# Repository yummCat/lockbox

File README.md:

# lockbox

The latest brilliant innovation we were able to come up with, was a box, that locks! 🤯

This device was meant to be small and cute, and importantly baby friendly. Designed for baby professionals, colloquially known as "Boss Babies" this device is meant to be carried around in a briefcase, unlocked with an RFID badge and four digit pin. In the process we learned a lot about RFID and how encryption worked(when we got sidetracked).

This project started with a schematic:

Next we made the pcb design:

Next we made the 3d model:

Lastly the BOM:

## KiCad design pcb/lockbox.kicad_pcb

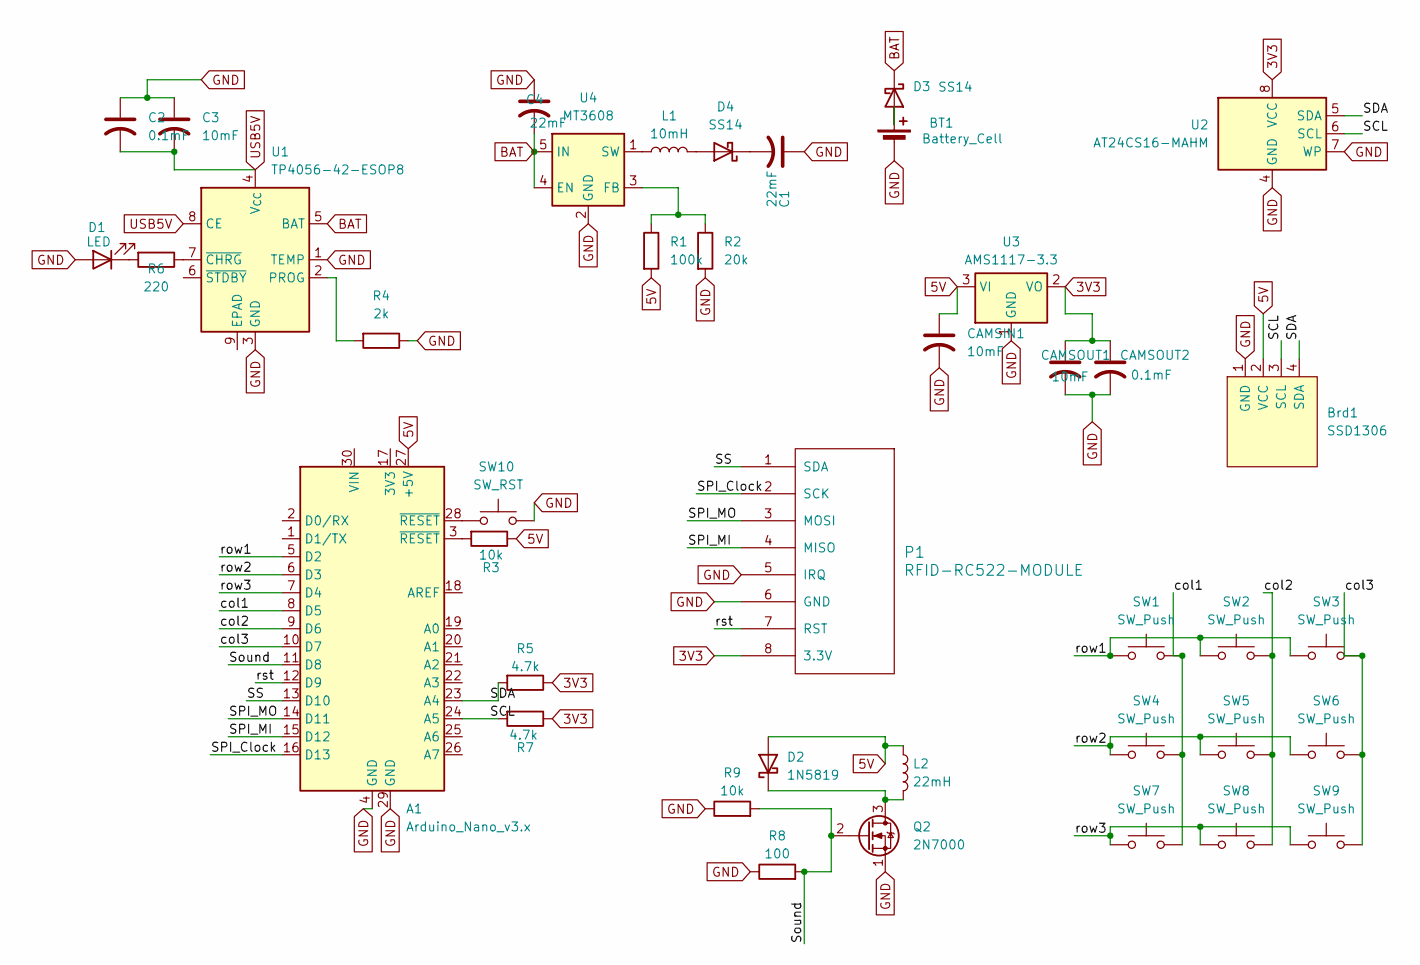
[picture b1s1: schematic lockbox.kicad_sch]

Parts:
A1: Arduino_Nano_v3.x; Arduino_Nano
BT1: Battery_Cell; JST_PH_S2B-PH-K_1x02_P2.00mm_Horizontal
Brd1: SSD1306; Adafruit_SSD1306
C1, C4: 22mF; CP_Radial_D5.0mm_P2.00mm
C2: 0.1mF; CP_Radial_D5.0mm_P2.50mm
C3: 10mF; CP_Radial_D5.0mm_P2.00mm
CAMSIN1: 10mF; CP_Radial_D5.0mm_P2.00mm
CAMSOUT1: 10mF; CP_Radial_D5.0mm_P2.00mm
CAMSOUT2: 0.1mF; CP_Radial_D5.0mm_P2.50mm
D1: LED; LED_D5.0mm
D2: 1N5819; D_DO-41_SOD81_P10.16mm_Horizontal
D3, D4: SS14; D_SMA
L1: 10mH; L_Axial_L26.0mm_D9.0mm_P5.08mm_Vertical_Fastron_77A
L2: 22mH; L_Axial_L26.0mm_D9.0mm_P5.08mm_Vertical_Fastron_77A
P1: RFID-RC522-MODULE; RC522_I2C_B30x20mm
Q2: 2N7000; TO-92L_Inline_Wide
R1: 100k; R_Axial_DIN0207_L6.3mm_D2.5mm_P7.62mm_Horizontal
R2: 20k; R_Axial_DIN0207_L6.3mm_D2.5mm_P7.62mm_Horizontal
R3, R9: 10k; R_Axial_DIN0207_L6.3mm_D2.5mm_P7.62mm_Horizontal
R4: 2k; R_Axial_DIN0207_L6.3mm_D2.5mm_P7.62mm_Horizontal
R5, R7: 4.7k; R_Axial_DIN0207_L6.3mm_D2.5mm_P7.62mm_Horizontal
R6: 220; R_Axial_DIN0207_L6.3mm_D2.5mm_P7.62mm_Horizontal
R8: 100; R_Axial_DIN0207_L6.3mm_D2.5mm_P7.62mm_Horizontal
SW1, SW2, SW3, SW4, SW5, SW6, SW7, SW8, SW9: SW_Push; SW_Cherry_MX_1.00u_PCB
SW10: SW_RST; SW_Cherry_MX_1.00u_PCB
U1: TP4056-42-ESOP8; SOIC-8-1EP_3.9x4.9mm_P1.27mm_EP2.41x3.3mm_ThermalVias
U2: AT24CS16-MAHM; DFN-8-1EP_3x2mm_P0.5mm_EP1.3x1.5mm
U3: AMS1117-3.3; SOT-223-3_TabPin2
U4: MT3608; SOT-23-6

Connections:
3V3: CAMSOUT1.1, CAMSOUT2.1, P1.8 (3.3V), R5.1, R7.1, U2.8 (VCC), U3.2 (VO)
5V: A1.27 (+5V), Brd1.2 (VCC), CAMSIN1.1, D2.2 (A), L2.1, R1.2, R3.1, U3.3 (VI)
/SCL: A1.24 (A5), Brd1.3 (SCL), R7.2, U2.6 (SCL)
/SDA: A1.23 (A4), Brd1.4 (SDA), R5.2, U2.5 (SDA)
/SPI_Clock: A1.16 (D13), P1.2 (SCK)
/SPI_MI: A1.15 (D12), P1.4 (MISO)
/SPI_MO: A1.14 (D11), P1.3 (MOSI)
/SS: A1.13 (D10), P1.1 (SDA)
/Sound: A1.11 (D8), Q2.2 (G), R8.2, R9.2
/col1: A1.8 (D5), SW1.2, SW4.2, SW7.2
/col2: A1.9 (D6), SW2.2, SW5.2, SW8.2
/col3: A1.10 (D7), SW3.2, SW6.2, SW9.2
/row1: A1.5 (D2), SW1.1, SW2.1, SW3.1
/row2: A1.6 (D3), SW4.1, SW5.1, SW6.1
/row3: A1.7 (D4), SW7.1, SW8.1, SW9.1
/rst: A1.12 (D9), P1.7 (RST)
BAT: C4.2, D3.1 (K), U1.5 (BAT), U4.4 (EN), U4.5 (IN)
GND: A1.4 (GND), A1.29 (GND), BT1.2 (-), Brd1.1 (GND), C1.1, C2.1, C3.1, C4.1, CAMSIN1.2, CAMSOUT1.2, CAMSOUT2.2, D1.2 (A), P1.5 (IRQ), P1.6 (GND), Q2.1 (S), R2.2, R4.1, R8.1, R9.1, SW10.2, U1.1 (TEMP), U1.3 (GND), U2.4 (GND), U2.7 (WP), U3.1 (GND), U4.2 (GND)
unnamed: A1.3 (~RESET), R3.2
unnamed: A1.28 (~RESET), SW10.1
unnamed: BT1.1 (+), D3.2 (A)
unnamed: D1.1 (K), R6.2
unnamed: D2.1 (K), L2.2, Q2.3 (D)
unnamed: D4.2 (A), L1.2
unnamed: C1.2, D4.1 (K)
unnamed: R4.2, U1.2 (PROG)
unnamed: R6.1, U1.7 (~CHRG)
unnamed: R1.1, R2.1, U4.3 (FB)
unnamed: L1.1, U4.1 (SW)
USB5V: C2.2, C3.2, U1.4 (V_{CC}), U1.8 (CE)

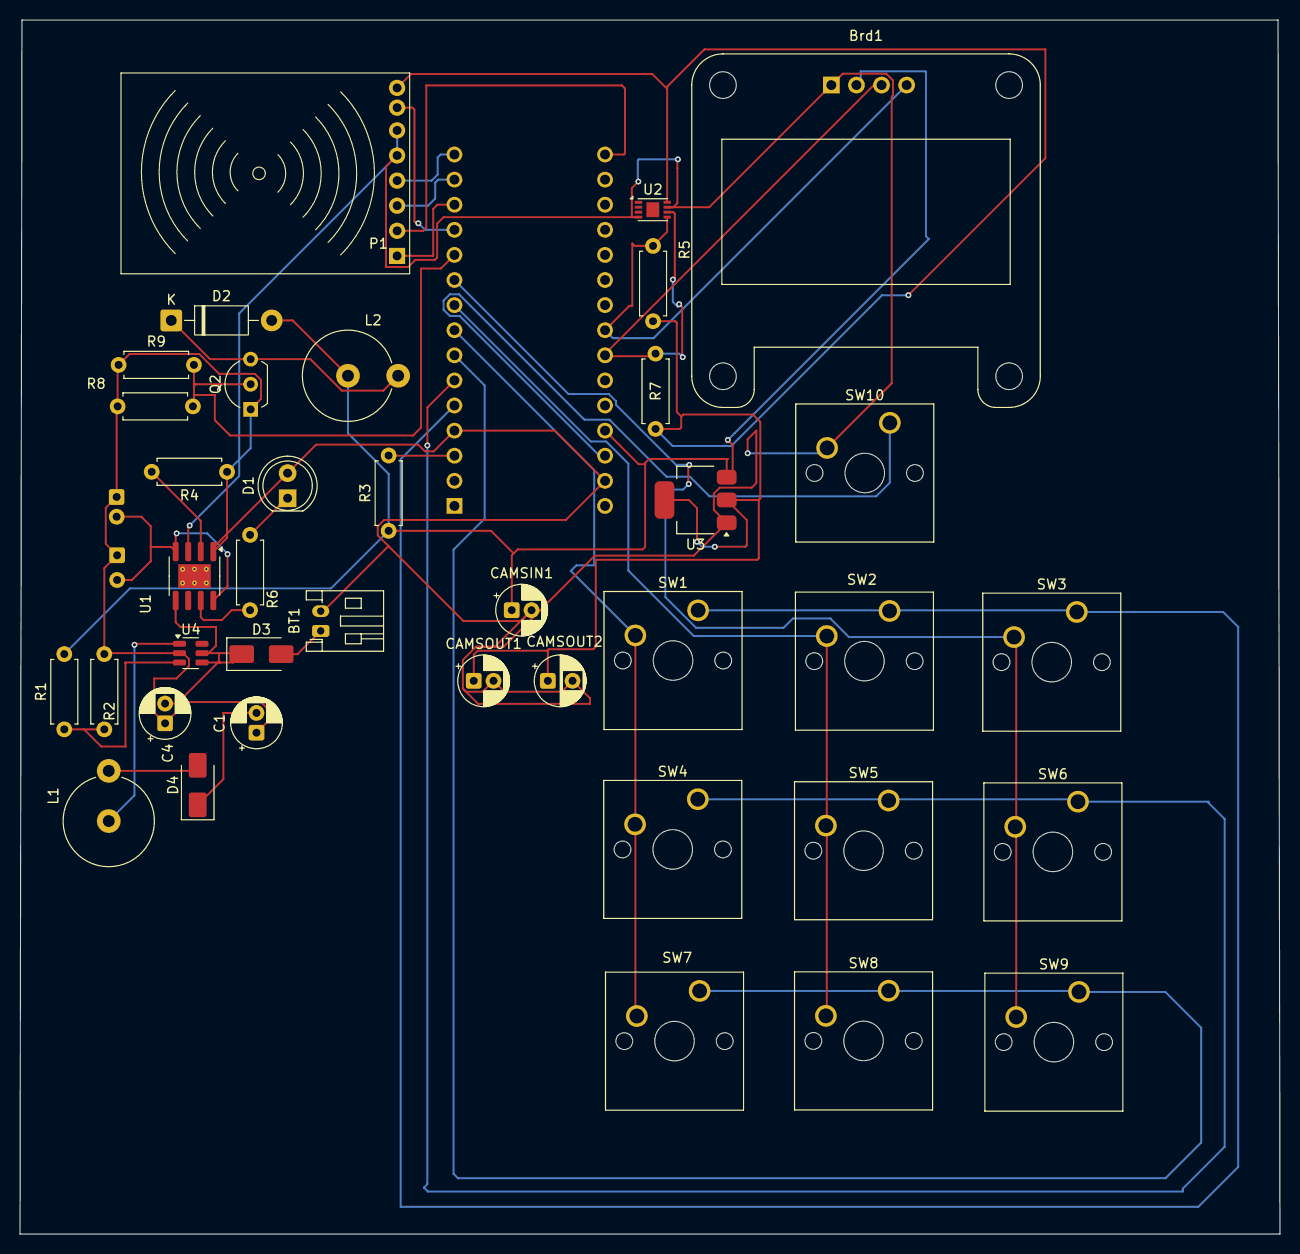
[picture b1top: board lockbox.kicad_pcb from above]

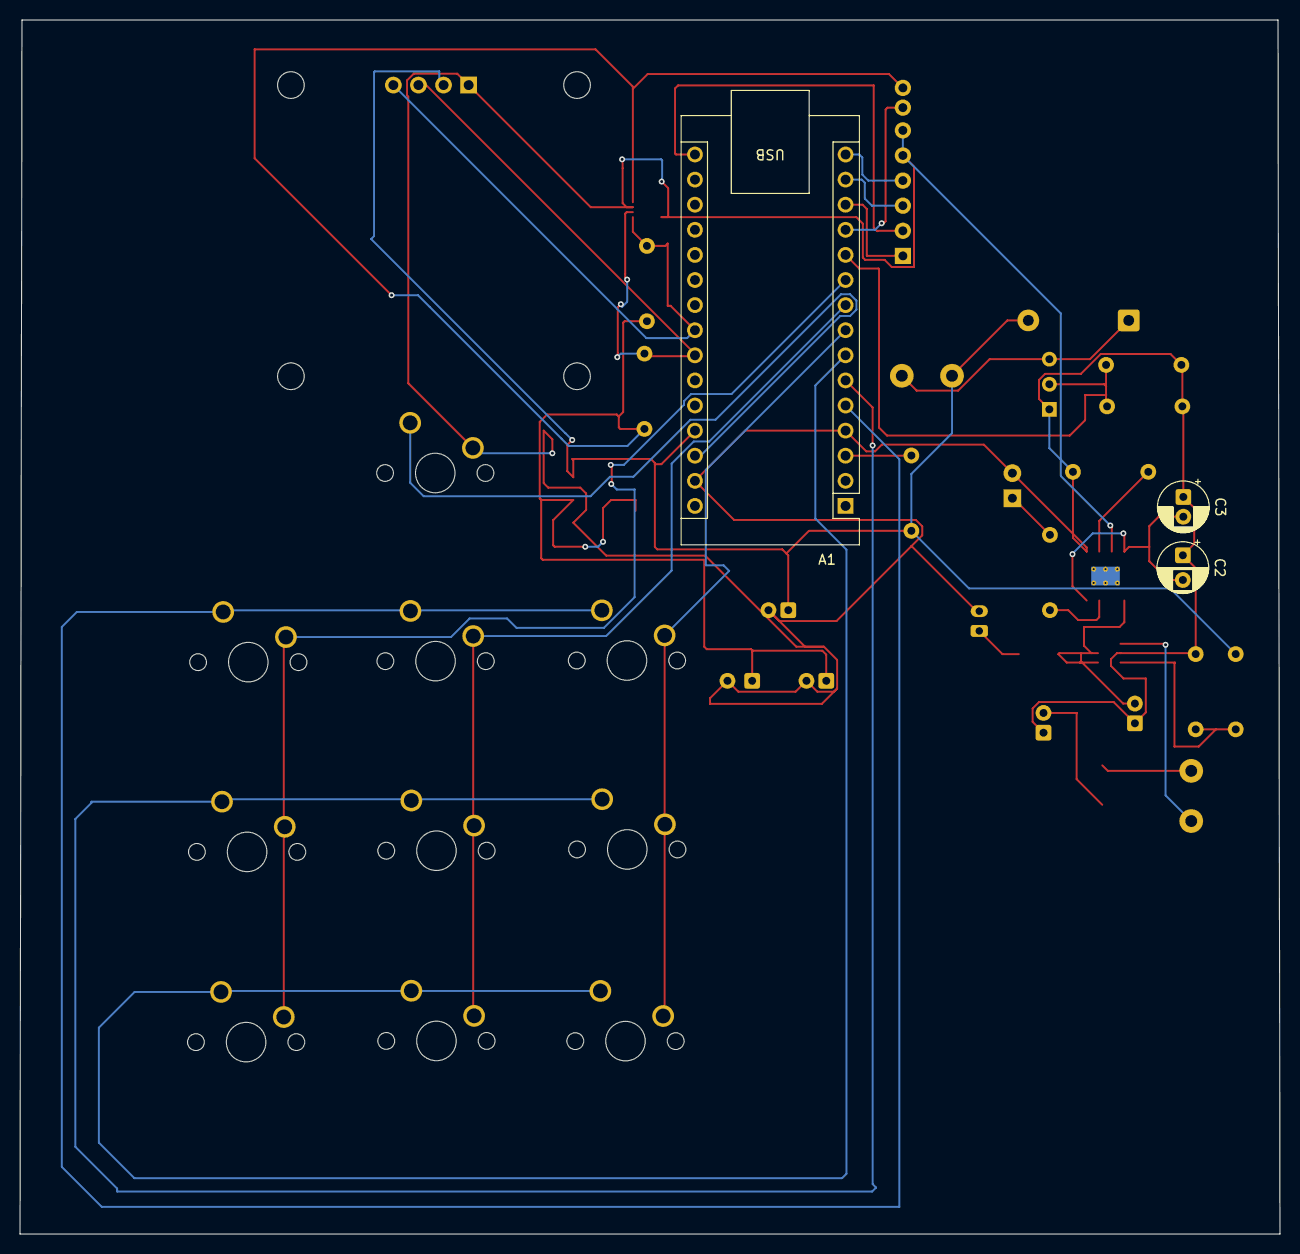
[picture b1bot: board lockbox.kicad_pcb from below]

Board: 2 copper layers, 127.5 x 122.8 mm, 41 parts (3 on the bottom side), 30 nets.

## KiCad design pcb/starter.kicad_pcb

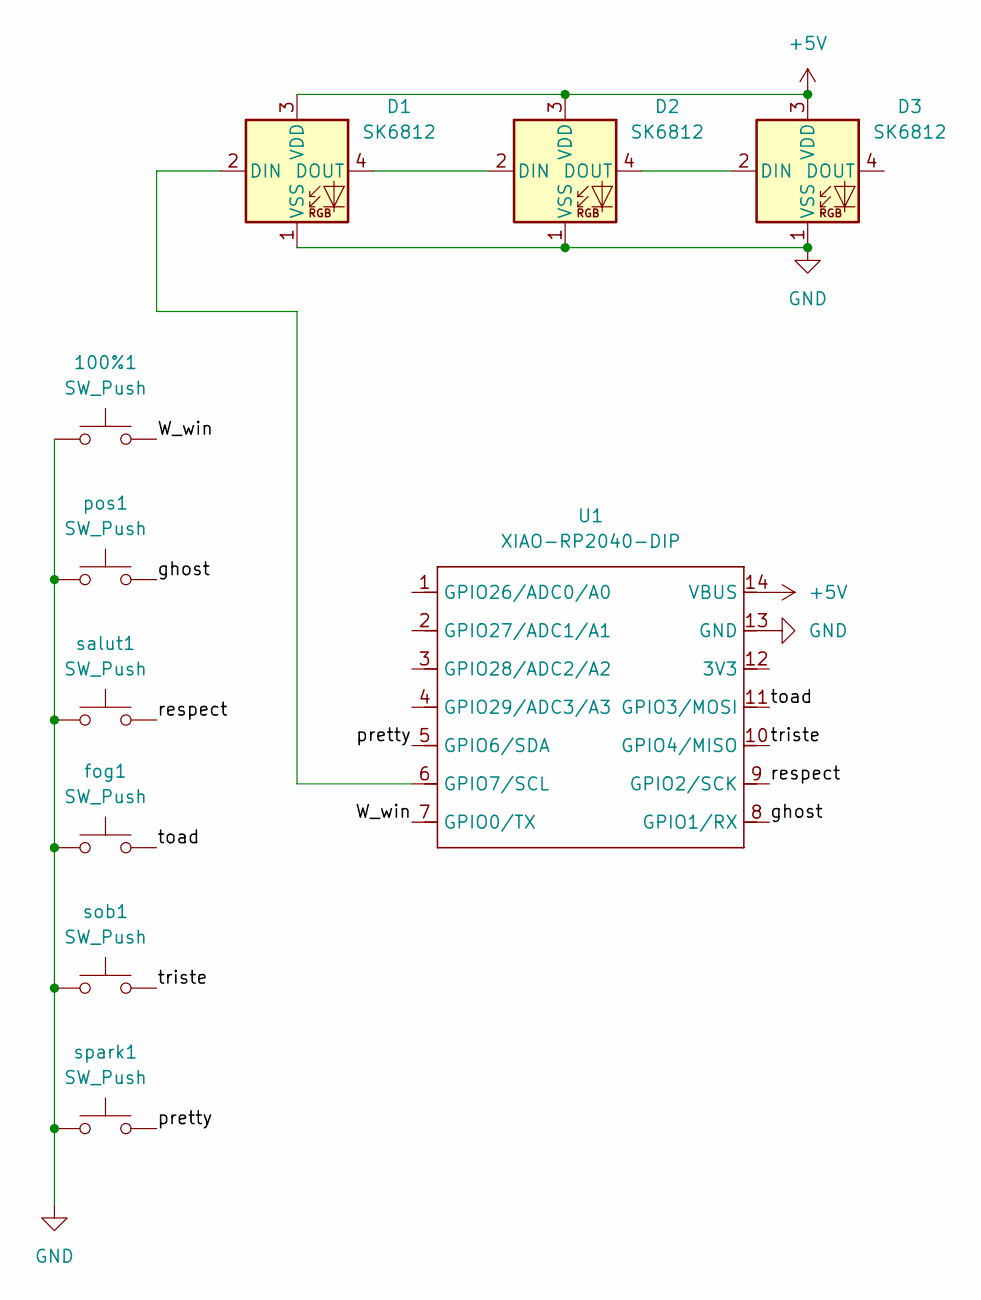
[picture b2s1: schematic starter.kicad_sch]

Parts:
100%1: SW_Push; SW_Cherry_MX_1.00u_PCB
D1, D2, D3: SK6812; LED_SK6812_PLCC4_5.0x5.0mm_P3.2mm
U1: XIAO-RP2040-DIP; XIAOLONGBAO
fog1: SW_Push; SW_Cherry_MX_1.00u_PCB
pos1: SW_Push; SW_Cherry_MX_1.00u_PCB
salut1: SW_Push; SW_Cherry_MX_1.00u_PCB
sob1: SW_Push; SW_Cherry_MX_1.00u_PCB
spark1: SW_Push; SW_Cherry_MX_1.00u_PCB

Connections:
+5V: D1.3 (VDD), D2.3 (VDD), D3.3 (VDD), U1.14 (VBUS)
/W_win: 100%1.2, U1.7 (GPIO0/TX)
/ghost: U1.8 (GPIO1/RX), pos1.2
/pretty: U1.5 (GPIO6/SDA), spark1.2
/respect: U1.9 (GPIO2/SCK), salut1.2
/toad: U1.11 (GPIO3/MOSI), fog1.2
/triste: U1.10 (GPIO4/MISO), sob1.2
GND: 100%1.1, D1.1 (VSS), D2.1 (VSS), D3.1 (VSS), U1.13 (GND), fog1.1, pos1.1, salut1.1, sob1.1, spark1.1
unnamed: D1.2 (DIN), U1.6 (GPIO7/SCL)
unnamed: D1.4 (DOUT), D2.2 (DIN)
unnamed: D2.4 (DOUT), D3.2 (DIN)

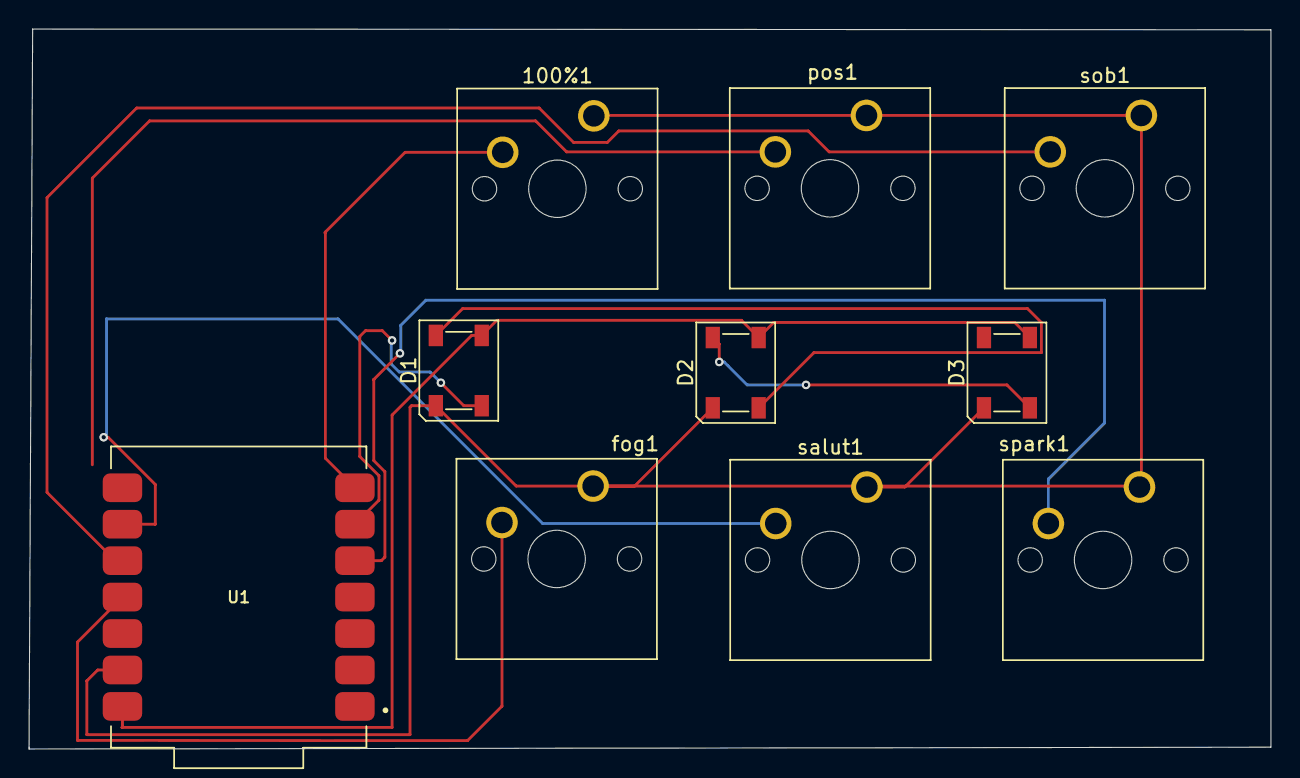
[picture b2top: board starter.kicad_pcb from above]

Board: 2 copper layers, 86.6 x 50.2 mm, 10 parts (0 on the bottom side), 11 nets.

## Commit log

2025-07-01 Added folders
2025-07-01 oopsie daisy weird folder placement
2025-07-01 fixed weird folder placement
2025-07-03 folders!
2025-07-03 help
2025-07-03 idk whats going on anymore
2025-07-03 added cad files
2025-07-03 adding stuff to production
2025-07-03 Add gerbers, top case, EMO STPs, and firmware to production folder
2025-07-03 Restore lockbox production files
2025-07-03 firmware folder!
2025-07-07 added complete cad file
2025-07-29 added bom csv file
